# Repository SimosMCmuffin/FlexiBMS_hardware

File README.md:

# Note, this is not the hardware version of the "Lite"-version of the FlexiBMS, but an earlier tested and discontinued/abandoned concept of the BMS design. Lite HW is a new project that was started after this HW project was discontinued and is not currently in open-source circulation HW design wise.

# FlexiBMS_hardware
Open Source BMS developed by Simo Sihvonen (Simos MCmuffin) with the Esk8 community, for the Esk8 community.

This project was inspired by Raphael Chang's Battman project's hardware design (https://github.com/raphaelchang/battman-hardware)

More current news and happening related to this project can be found and followed over at the project thread at the electic-skateboard.builders forum: 
http://www.electric-skateboard.builders/t/flexibms-0-2-hw-under-work-flexible-configuration-and-charging-bms/46117

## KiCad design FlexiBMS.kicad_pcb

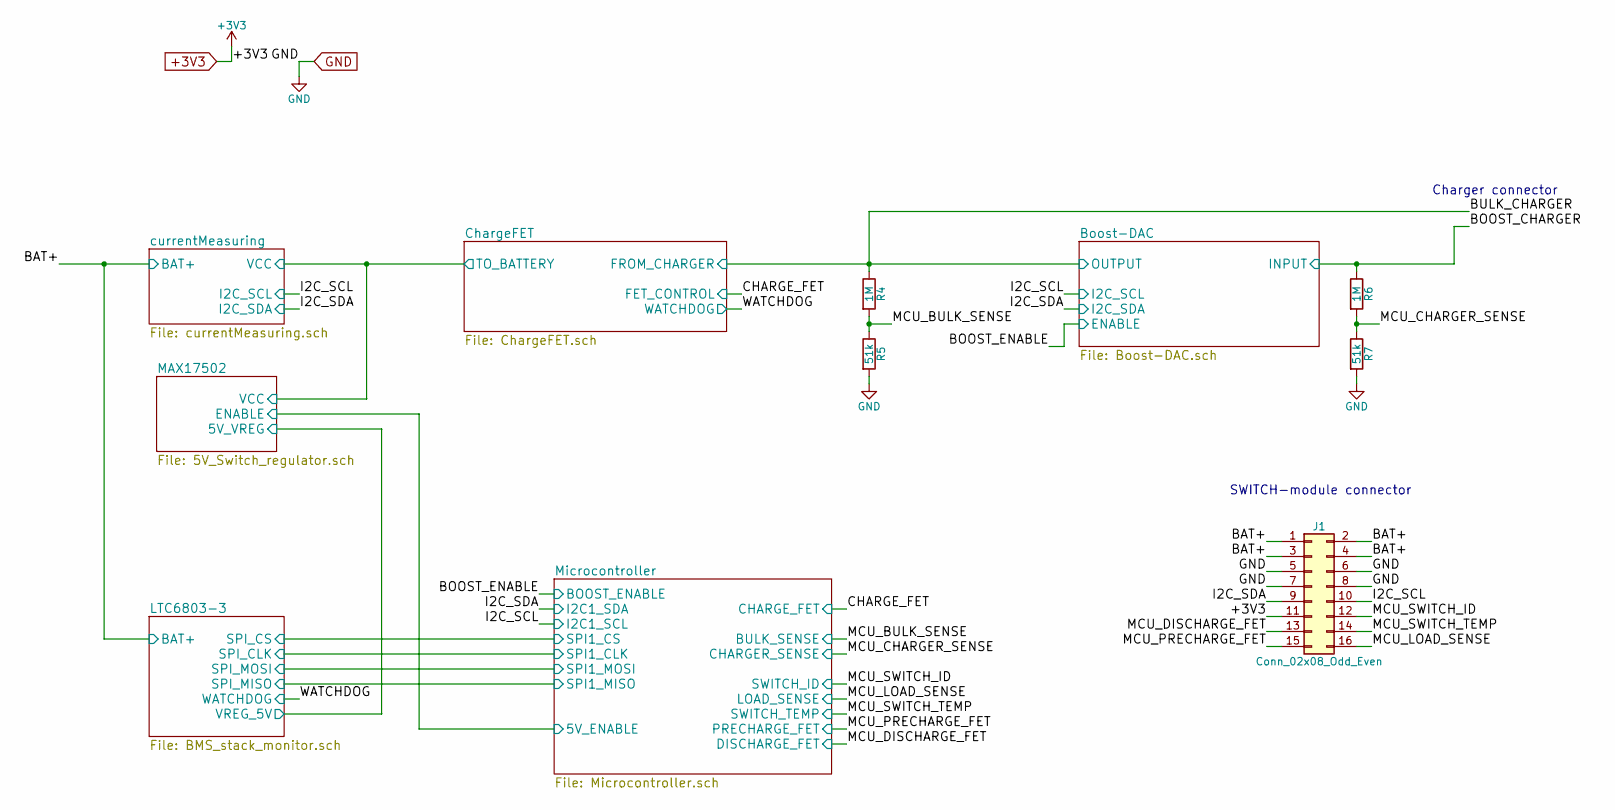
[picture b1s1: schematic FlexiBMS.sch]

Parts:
J1: Conn_02x08_Odd_Even; Pin_Header_Straight_2x08_Pitch2.54mm
R4, R6: 1M; R_0603
R5, R7: 51k; R_0603

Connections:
+3V3: J1.11; also elsewhere on the board
/BAT+: J1.1, J1.2, J1.3, J1.4; also elsewhere on the board
/BOOST_CHARGER: R6.1; also elsewhere on the board
/BULK_CHARGER: R4.1; also elsewhere on the board
/I2C_SCL: J1.10; also elsewhere on the board
/I2C_SDA: J1.9; also elsewhere on the board
/MCU_BULK_SENSE: R4.2, R5.1; also elsewhere on the board
/MCU_CHARGER_SENSE: R6.2, R7.1; also elsewhere on the board
/MCU_DISCHARGE_FET: J1.13; also elsewhere on the board
/MCU_LOAD_SENSE: J1.16; also elsewhere on the board
/MCU_PRECHARGE_FET: J1.15; also elsewhere on the board
/MCU_SWITCH_ID: J1.12; also elsewhere on the board
/MCU_SWITCH_TEMP: J1.14; also elsewhere on the board
GND: J1.5, J1.6, J1.7, J1.8, R5.2, R7.2; also elsewhere on the board

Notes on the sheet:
SWITCH-module connector
Charger connector

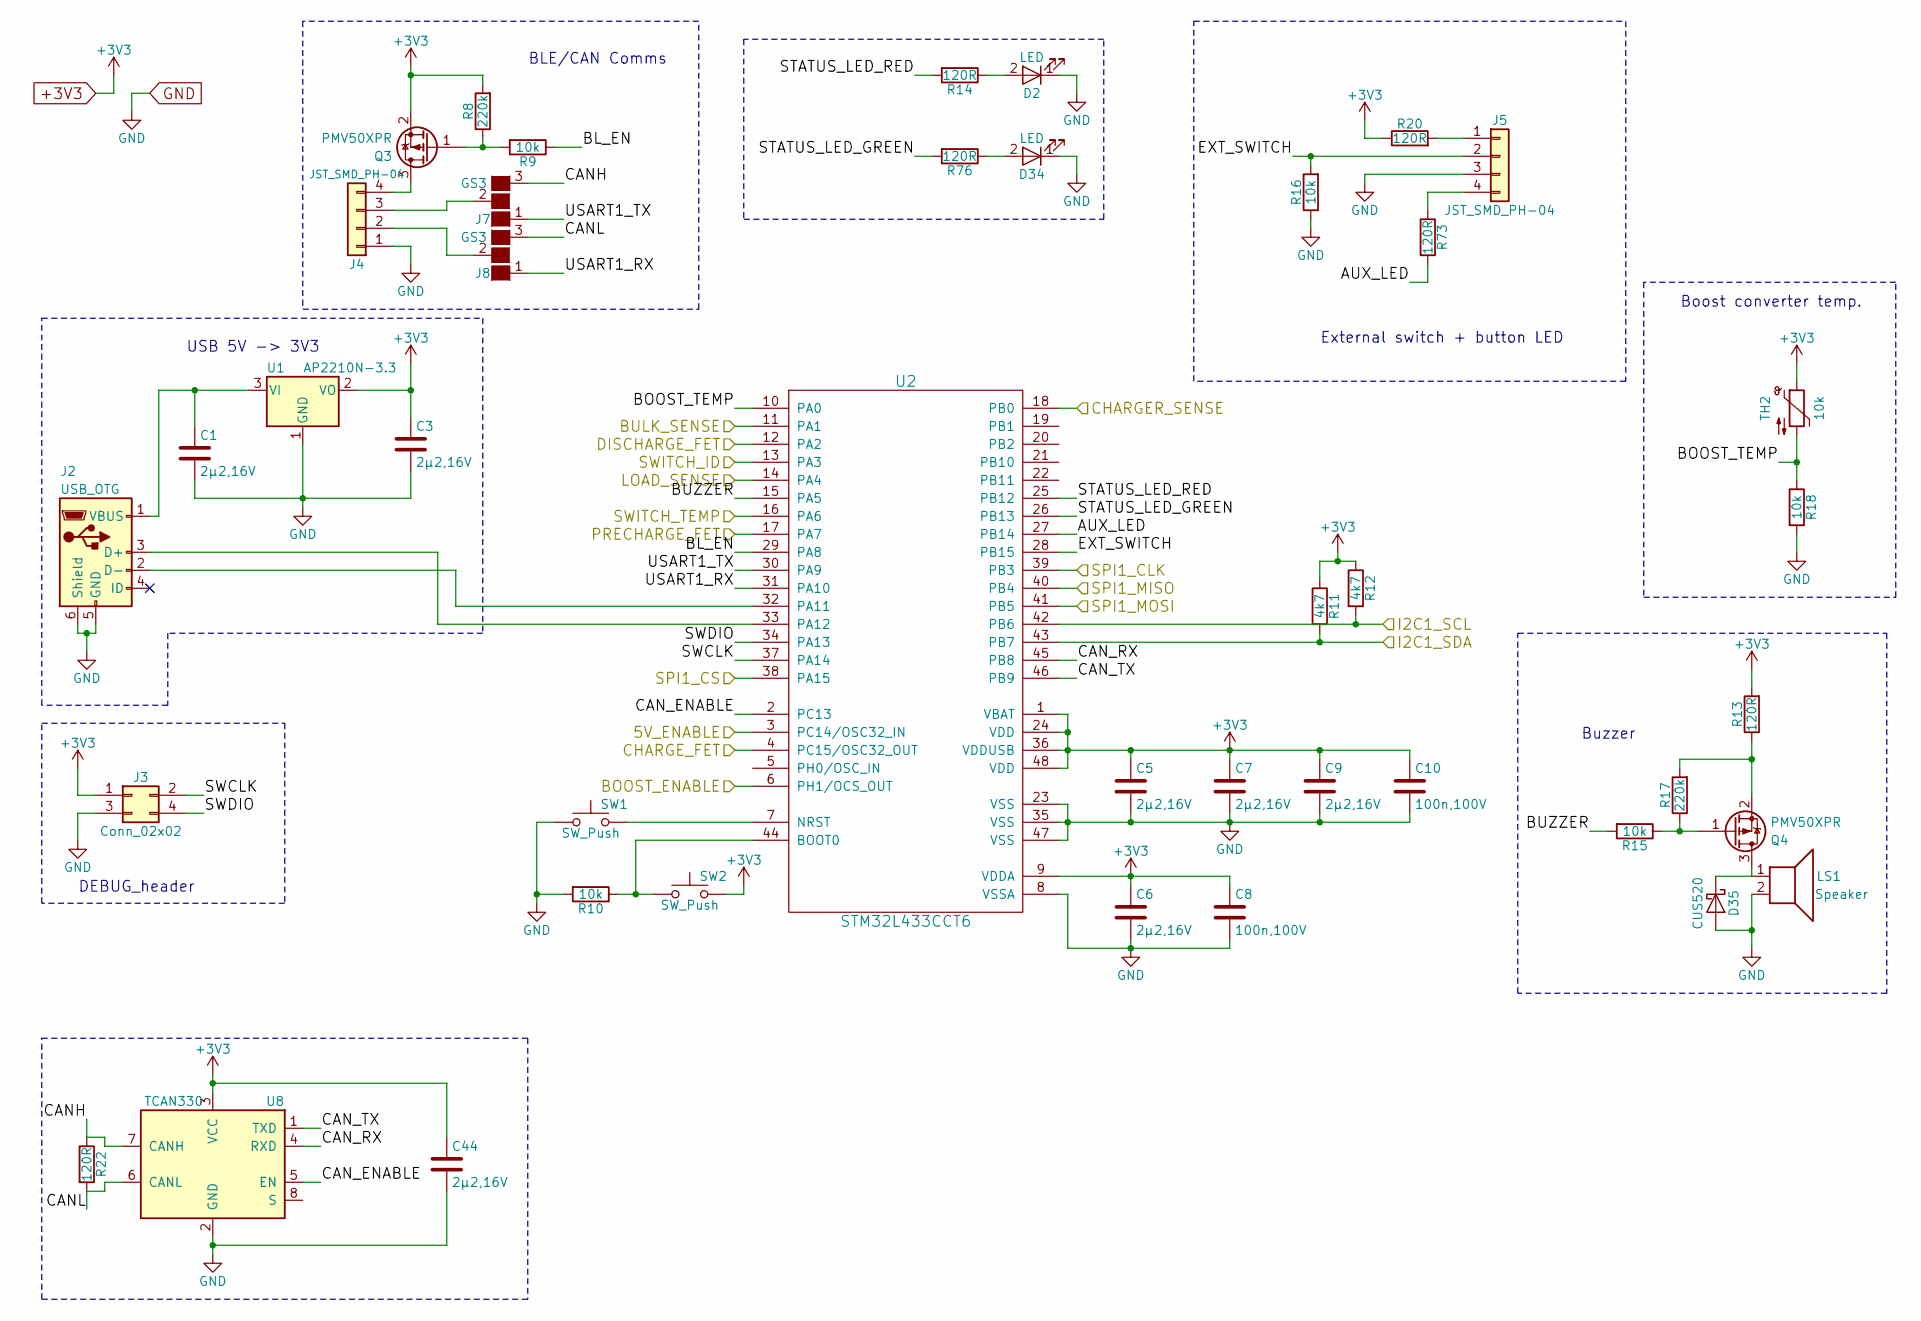
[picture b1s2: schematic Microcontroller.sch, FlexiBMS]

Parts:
C1, C3, C5, C6, C7, C9, C44: 2µ2,16V; C_0603
C8, C10: 100n,100V; C_0603
D2, D34: LED; LED_0603
D35: CUS520; D_SOD-323
J2: USB_OTG; USB_Micro-B_Molex_47346-0001
J3: Conn_02x02; Socket_Strip_Straight_2x02_Pitch2.54mm_SMD
J4, J5: JST_SMD_PH-04; JST_PH_B4B-PH-SM4-TB_04x2.00mm_Straight
J7, J8: GS3
LS1: Speaker; CSS-0575
Q3, Q4: PMV50XPR; SOT-23
R8, R17: 220k; R_0603
R9, R10, R15, R16, R18: 10k; R_0603
R11, R12: 4k7; R_0603
R13, R14, R20, R22, R73, R76: 120R; R_0603
SW1, SW2: SW_Push; SW_SPST_PTS810
TH2: 10k; R_0603
U1: AP2210N-3.3; SOT-23
U2: STM32L433CCT6; LQFP-48_7x7mm_Pitch0.5mm
U8: TCAN330; SOT-23-8

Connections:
+3V3: C3.1, C5.1, C6.1, C7.1, C8.1, C9.1, C10.1, C44.1, J3.1, Q3.2 (S), R8.2, R11.1, R12.1, R13.2, R20.1, SW2.2, TH2.1, U1.2 (VO), U2.1 (VBAT), U2.9 (VDDA), U2.24 (VDD), U2.36 (VDDUSB), U2.48 (VDD), U8.3 (VCC); also elsewhere on the board
/BOOST_ENABLE: U2.6 (PH1/OCS_OUT); also elsewhere on the board
/CHARGE_FET: U2.4 (PC15/OSC32_OUT); also elsewhere on the board
/I2C_SCL: R12.2, U2.42 (PB6); also elsewhere on the board
/I2C_SDA: R11.2, U2.43 (PB7); also elsewhere on the board
/MCU_BULK_SENSE: U2.11 (PA1); also elsewhere on the board
/MCU_CHARGER_SENSE: U2.18 (PB0); also elsewhere on the board
/MCU_DISCHARGE_FET: U2.12 (PA2); also elsewhere on the board
/MCU_LOAD_SENSE: U2.14 (PA4); also elsewhere on the board
/MCU_PRECHARGE_FET: U2.17 (PA7); also elsewhere on the board
/MCU_SWITCH_ID: U2.13 (PA3); also elsewhere on the board
/MCU_SWITCH_TEMP: U2.16 (PA6); also elsewhere on the board
/Microcontroller/5V_ENABLE: U2.3 (PC14/OSC32_IN); also elsewhere on the board
/Microcontroller/AUX_LED: R73.2, U2.27 (PB14)
/Microcontroller/BL_EN: R9.1, U2.29 (PA8)
/Microcontroller/BOOST_TEMP: R18.1, TH2.2, U2.10 (PA0)
/Microcontroller/BUZZER: R15.2, U2.15 (PA5)
/Microcontroller/CANH: J7.3 (G3), R22.1, U8.7 (CANH)
/Microcontroller/CANL: J8.3 (G3), R22.2, U8.6 (CANL)
/Microcontroller/CAN_ENABLE: U2.2 (PC13), U8.5 (EN)
/Microcontroller/CAN_RX: U2.45 (PB8), U8.4 (RXD)
/Microcontroller/CAN_TX: U2.46 (PB9), U8.1 (TXD)
/Microcontroller/EXT_SWITCH: J5.2, R16.2, U2.28 (PB15)
/Microcontroller/SPI1_CLK: U2.39 (PB3); also elsewhere on the board
/Microcontroller/SPI1_CS: U2.38 (PA15); also elsewhere on the board
/Microcontroller/SPI1_MISO: U2.40 (PB4); also elsewhere on the board
/Microcontroller/SPI1_MOSI: U2.41 (PB5); also elsewhere on the board
/Microcontroller/STATUS_LED_GREEN: R76.2, U2.26 (PB13)
/Microcontroller/STATUS_LED_RED: R14.2, U2.25 (PB12)
/Microcontroller/SWCLK: J3.2, U2.37 (PA14)
/Microcontroller/SWDIO: J3.4, U2.34 (PA13)
/Microcontroller/USART1_RX: J8.1 (G1), U2.31 (PA10)
/Microcontroller/USART1_TX: J7.1 (G1), U2.30 (PA9)
GND: C1.2, C3.2, C5.2, C6.2, C7.2, C8.2, C9.2, C10.2, C44.2, D2.1 (K), D34.1 (K), D35.2 (A), J2.5 (GND), J2.6 (Shield), J3.3, J4.1, J5.3, LS1.2, R10.2, R16.1, R18.2, SW1.1, U1.1 (GND), U2.8 (VSSA), U2.23 (VSS), U2.35 (VSS), U2.47 (VSS), U8.2 (GND); also elsewhere on the board
unnamed: C1.1, J2.1 (VBUS), U1.3 (VI)
unnamed: D2.2 (A), R14.1
unnamed: D34.2 (A), R76.1
unnamed: D35.1 (K), LS1.1, Q4.3 (D)
unnamed: J2.2 (D-), U2.32 (PA11)
unnamed: J2.3 (D+), U2.33 (PA12)
unnamed: J4.2, J8.2 (G2)
unnamed: J4.3, J7.2 (G2)
unnamed: J4.4, Q3.3 (D)
unnamed: J5.1, R20.2
unnamed: J5.4, R73.1
unnamed: Q3.1 (G), R8.1, R9.2
unnamed: Q4.1 (G), R15.1, R17.1
unnamed: Q4.2 (S), R13.1, R17.2
unnamed: R10.1, SW2.1, U2.44 (BOOT0)
unnamed: SW1.2, U2.7 (NRST)

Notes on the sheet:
Boost converter temp.
External switch + button LED
BLE/CAN Comms
Buzzer
USB 5V -> 3V3
DEBUG_header

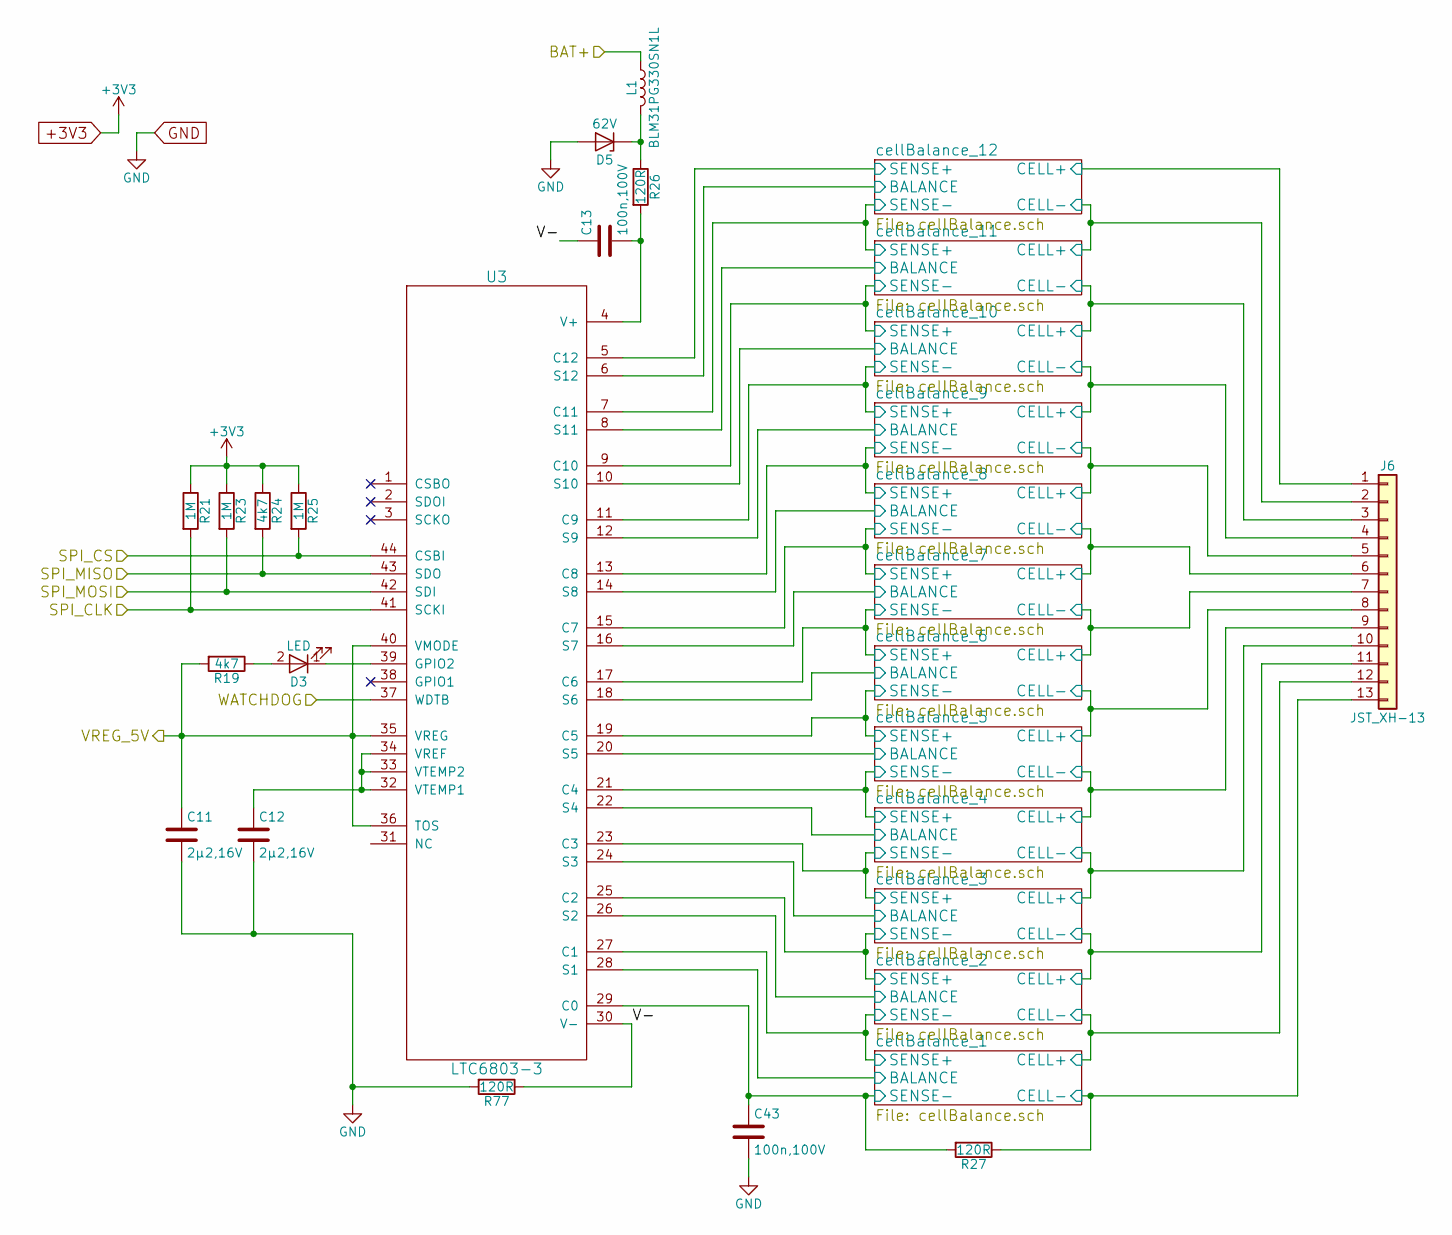
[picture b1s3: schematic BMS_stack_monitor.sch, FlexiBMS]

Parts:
C11, C12: 2µ2,16V; C_0603
C13, C43: 100n,100V; C_0603
D3: LED; LED_0603
D5: 62V; D_SOD-123
J6: JST_XH-13; JST_XH_S13B-XH-A_13x2.50mm_Angled
L1: BLM31PG330SN1L; L_1206
R19, R24: 4k7; R_0603
R21, R23, R25: 1M; R_0603
R26, R77: 120R; R_0603
R27: 120R; R_0402
U3: LTC6803-3; FSOP-44_5.3x13.0mm_Pitch0.5mm

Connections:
+3V3: R21.1, R23.1, R24.1, R25.1; also elsewhere on the board
/BAT+: L1.1; also elsewhere on the board
/LTC6803-3/V-: C13.1, R77.1, U3.30 (V-)
/LTC6803-3/cellBalance_1/BALANCE: U3.28 (S1); also elsewhere on the board
/LTC6803-3/cellBalance_1/CELL+: J6.12; also elsewhere on the board
/LTC6803-3/cellBalance_1/CELL-: J6.13, R27.1; also elsewhere on the board
/LTC6803-3/cellBalance_1/SENSE+: U3.27 (C1); also elsewhere on the board
/LTC6803-3/cellBalance_1/SENSE-: C43.1, R27.2, U3.29 (C0); also elsewhere on the board
/LTC6803-3/cellBalance_2/BALANCE: U3.26 (S2); also elsewhere on the board
/LTC6803-3/cellBalance_2/CELL+: J6.11; also elsewhere on the board
/LTC6803-3/cellBalance_2/SENSE+: U3.25 (C2); also elsewhere on the board
/LTC6803-3/cellBalance_3/BALANCE: U3.24 (S3); also elsewhere on the board
/LTC6803-3/cellBalance_3/CELL+: J6.10; also elsewhere on the board
/LTC6803-3/cellBalance_3/SENSE+: U3.23 (C3); also elsewhere on the board
/LTC6803-3/cellBalance_4/BALANCE: U3.22 (S4); also elsewhere on the board
/LTC6803-3/cellBalance_4/CELL+: J6.9; also elsewhere on the board
/LTC6803-3/cellBalance_4/SENSE+: U3.21 (C4); also elsewhere on the board
/LTC6803-3/cellBalance_5/BALANCE: U3.20 (S5); also elsewhere on the board
/LTC6803-3/cellBalance_5/CELL+: J6.8; also elsewhere on the board
/LTC6803-3/cellBalance_5/SENSE+: U3.19 (C5); also elsewhere on the board
/LTC6803-3/cellBalance_6/BALANCE: U3.18 (S6); also elsewhere on the board
/LTC6803-3/cellBalance_6/CELL+: J6.7; also elsewhere on the board
/LTC6803-3/cellBalance_6/SENSE+: U3.17 (C6); also elsewhere on the board
/LTC6803-3/cellBalance_7/BALANCE: U3.16 (S7); also elsewhere on the board
/LTC6803-3/cellBalance_7/CELL+: J6.6; also elsewhere on the board
/LTC6803-3/cellBalance_7/SENSE+: U3.15 (C7); also elsewhere on the board
/LTC6803-3/cellBalance_8/BALANCE: U3.14 (S8); also elsewhere on the board
/LTC6803-3/cellBalance_8/CELL+: J6.5; also elsewhere on the board
/LTC6803-3/cellBalance_8/SENSE+: U3.13 (C8); also elsewhere on the board
/LTC6803-3/cellBalance_9/BALANCE: U3.12 (S9); also elsewhere on the board
/LTC6803-3/cellBalance_9/CELL+: J6.4; also elsewhere on the board
/LTC6803-3/cellBalance_9/SENSE+: U3.11 (C9); also elsewhere on the board
/LTC6803-3/cellBalance_10/BALANCE: U3.10 (S10); also elsewhere on the board
/LTC6803-3/cellBalance_10/CELL+: J6.3; also elsewhere on the board
/LTC6803-3/cellBalance_10/SENSE+: U3.9 (C10); also elsewhere on the board
/LTC6803-3/cellBalance_11/BALANCE: U3.8 (S11); also elsewhere on the board
/LTC6803-3/cellBalance_11/CELL+: J6.2; also elsewhere on the board
/LTC6803-3/cellBalance_11/SENSE+: U3.7 (C11); also elsewhere on the board
/LTC6803-3/cellBalance_12/BALANCE: U3.6 (S12); also elsewhere on the board
/LTC6803-3/cellBalance_12/CELL+: J6.1; also elsewhere on the board
/LTC6803-3/cellBalance_12/SENSE+: U3.5 (C12); also elsewhere on the board
/MAX17502/5V_VREG: C11.1, R19.2, U3.35 (VREG), U3.36 (TOS), U3.40 (VMODE); also elsewhere on the board
/Microcontroller/SPI1_CLK: R21.2, U3.41 (SCKI); also elsewhere on the board
/Microcontroller/SPI1_CS: R25.2, U3.44 (CSBI); also elsewhere on the board
/Microcontroller/SPI1_MISO: R24.2, U3.43 (SDO); also elsewhere on the board
/Microcontroller/SPI1_MOSI: R23.2, U3.42 (SDI); also elsewhere on the board
/WATCHDOG: U3.37 (WDTB); also elsewhere on the board
GND: C11.2, C12.2, C43.2, D5.2 (A), R77.2; also elsewhere on the board
unnamed: C12.1, U3.32 (VTEMP1), U3.33 (VTEMP2), U3.34 (VREF)
unnamed: C13.2, R26.2, U3.4 (V+)
unnamed: D3.1 (K), U3.39 (GPIO2)
unnamed: D3.2 (A), R19.1
unnamed: D5.1 (K), L1.2, R26.1

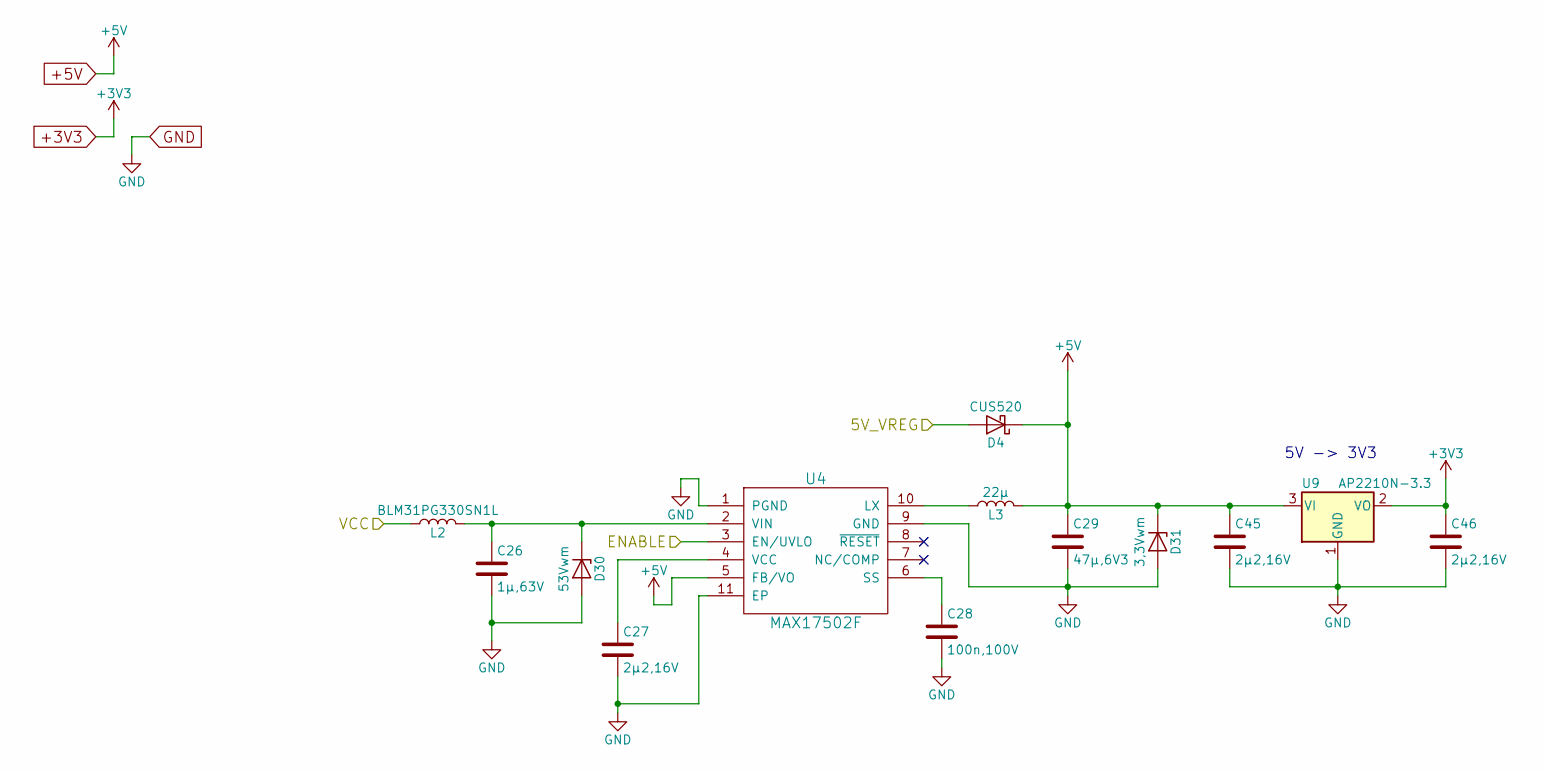
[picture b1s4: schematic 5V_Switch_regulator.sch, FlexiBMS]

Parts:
C26: 1µ,63V; C_1210
C27, C45, C46: 2µ2,16V; C_0603
C28: 100n,100V; C_0603
C29: 47µ,6V3; C_1206
D4: CUS520; D_SOD-323
D30: 53Vwm; D_SMA
D31: 3,3Vwm; D_SOD-123F
L2: BLM31PG330SN1L; L_1206
L3: 22µ; L_1210
U4: MAX17502F; DFN-10-1EP_2x3mm_Pitch0.5mm
U9: AP2210N-3.3; SOT-23

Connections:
+3V3: C46.1, U9.2 (VO); also elsewhere on the board
+5V: C29.1, C45.1, D4.1 (K), D31.1 (K), L3.2, U4.5 (FB/VO), U9.3 (VI)
/ChargeFET/TO_BATTERY: L2.1; also elsewhere on the board
/MAX17502/5V_VREG: D4.2 (A); also elsewhere on the board
/Microcontroller/5V_ENABLE: U4.3 (EN/UVLO); also elsewhere on the board
GND: C26.2, C27.2, C28.2, C29.2, C45.2, C46.2, D30.2 (A), D31.2 (A), U4.1 (PGND), U4.9 (GND), U4.11 (EP), U9.1 (GND); also elsewhere on the board
unnamed: C26.1, D30.1 (K), L2.2, U4.2 (VIN)
unnamed: C27.1, U4.4 (VCC)
unnamed: C28.1, U4.6 (SS)
unnamed: L3.1, U4.10 (LX)

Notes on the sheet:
5V -> 3V3

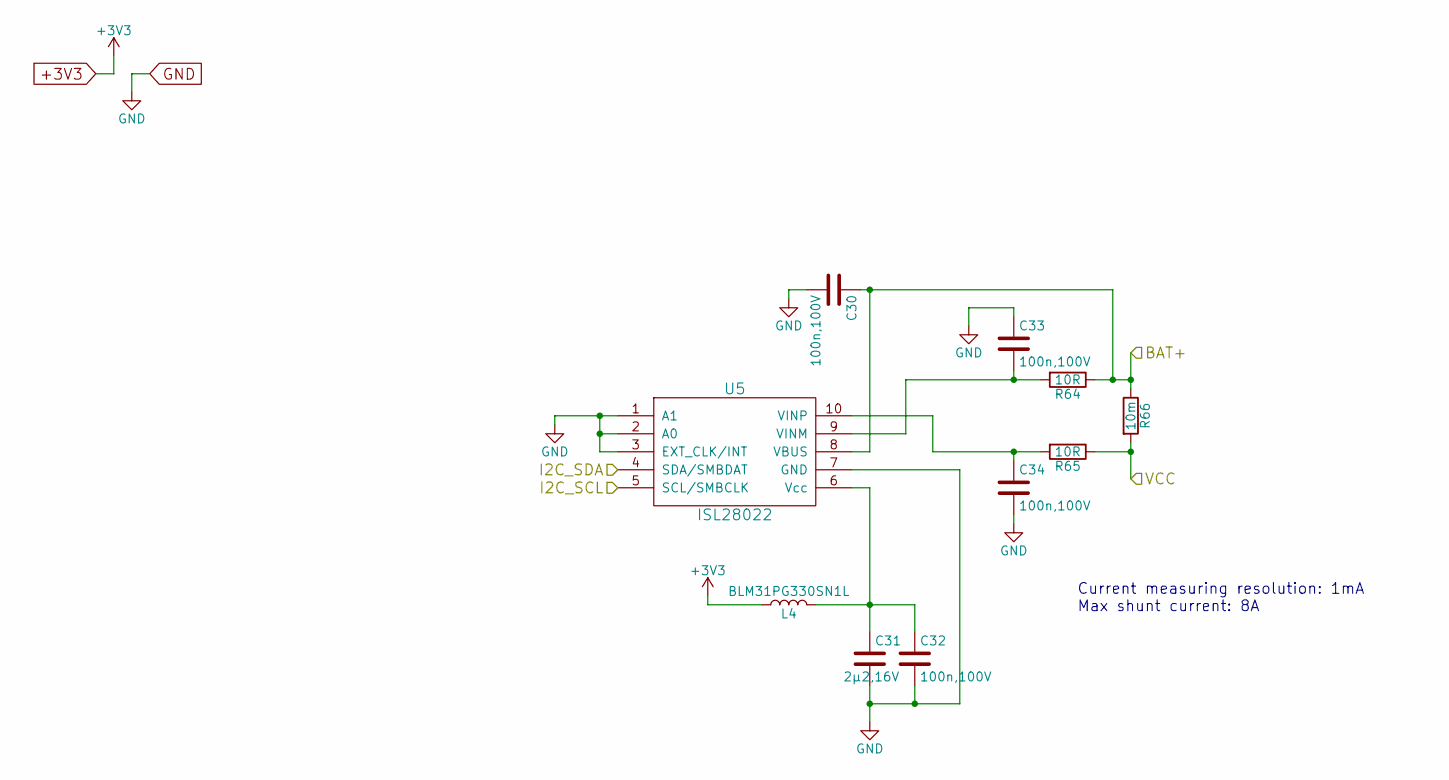
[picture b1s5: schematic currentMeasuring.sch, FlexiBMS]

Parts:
C30, C32, C33, C34: 100n,100V; C_0603
C31: 2µ2,16V; C_0603
L4: BLM31PG330SN1L; L_1206
R64, R65: 10R; R_0603
R66: 10m; R_1206
U5: ISL28022; MSOP-10_3x3mm_Pitch0.5mm

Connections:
+3V3: L4.1; also elsewhere on the board
/BAT+: C30.1, R64.1, R66.1, U5.8 (VBUS); also elsewhere on the board
/ChargeFET/TO_BATTERY: R65.1, R66.2; also elsewhere on the board
/I2C_SCL: U5.5 (SCL/SMBCLK); also elsewhere on the board
/I2C_SDA: U5.4 (SDA/SMBDAT); also elsewhere on the board
GND: C30.2, C31.2, C32.2, C33.1, C34.2, U5.1 (A1), U5.2 (A0), U5.3 (EXT_CLK/INT), U5.7 (GND); also elsewhere on the board
unnamed: C31.1, C32.1, L4.2, U5.6 (Vcc)
unnamed: C33.2, R64.2, U5.9 (VINM)
unnamed: C34.1, R65.2, U5.10 (VINP)

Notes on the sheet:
Current measuring resolution: 1mA Max shunt current: 8A

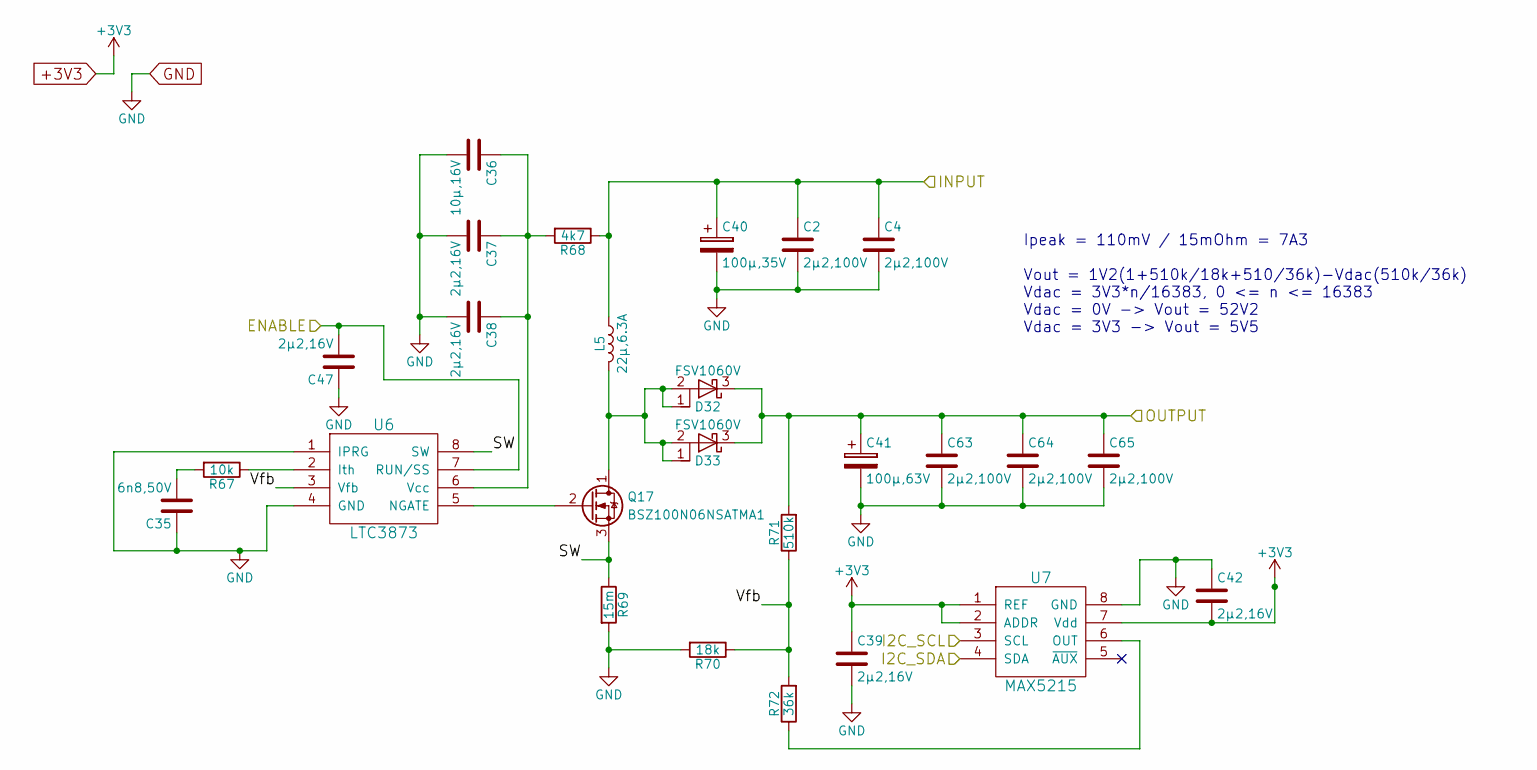
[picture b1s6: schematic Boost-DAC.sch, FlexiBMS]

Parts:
C2, C4, C63, C64, C65: 2µ2,100V; C_1210
C35: 6n8,50V; C_0603
C36: 10µ,16V; C_1206
C37, C38, C39, C42, C47: 2µ2,16V; C_0603
C40: 100µ,35V; CP_Elec_6.3x7.7
C41: 100µ,63V; CP_Elec_10x10
D32, D33: FSV1060V; TO-277A
L5: 22µ,6.3A; HC9
Q17: BSZ100N06NSATMA1; PG-TDSON-8
R67: 10k; R_0603
R68: 4k7; R_0603
R69: 15m; R_1206
R70: 18k; R_0603
R71: 510k; R_0603
R72: 36k; R_0603
U6: LTC3873; TSOT-23-8
U7: MAX5215; MSOP-8_3x3mm_Pitch0.65mm

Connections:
+3V3: C39.1, C42.2, U7.1 (REF), U7.2 (ADDR), U7.7 (Vdd); also elsewhere on the board
/BOOST_CHARGER: C2.1, C4.1, C40.1, L5.1, R68.1; also elsewhere on the board
/BOOST_ENABLE: C47.2, U6.7 (RUN/SS); also elsewhere on the board
/BULK_CHARGER: C41.1, C63.1, C64.1, C65.1, D32.3 (K), D33.3 (K), R71.2; also elsewhere on the board
/Boost-DAC/SW: Q17.3 (S), R69.1, U6.8 (SW)
/Boost-DAC/Vfb: R70.1, R71.1, R72.2, U6.3 (Vfb)
/I2C_SCL: U7.3 (SCL); also elsewhere on the board
/I2C_SDA: U7.4 (SDA); also elsewhere on the board
GND: C2.2, C4.2, C35.1, C36.2, C37.2, C38.2, C39.2, C40.2, C41.2, C42.1, C47.1, C63.2, C64.2, C65.2, R69.2, R70.2, U6.1 (IPRG), U6.4 (GND), U7.8 (GND); also elsewhere on the board
unnamed: C35.2, R67.2
unnamed: C36.1, C37.1, C38.1, R68.2, U6.6 (Vcc)
unnamed: D32.1 (A), D32.2 (A), D33.1 (A), D33.2 (A), L5.2, Q17.1 (D)
unnamed: Q17.2 (G), U6.5 (NGATE)
unnamed: R67.1, U6.2 (Ith)
unnamed: R72.1, U7.6 (OUT)

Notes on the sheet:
Ipeak = 110mV / 15mOhm = 7A3 Vout = 1V2(1+510k/18k+510/36k)-Vdac(510k/36k) Vdac = 3V3*n/16383, 0 <= n <= 16383 Vdac = 0V -> Vout = 52V2 Vdac = 3V3 -> Vout = 5V5

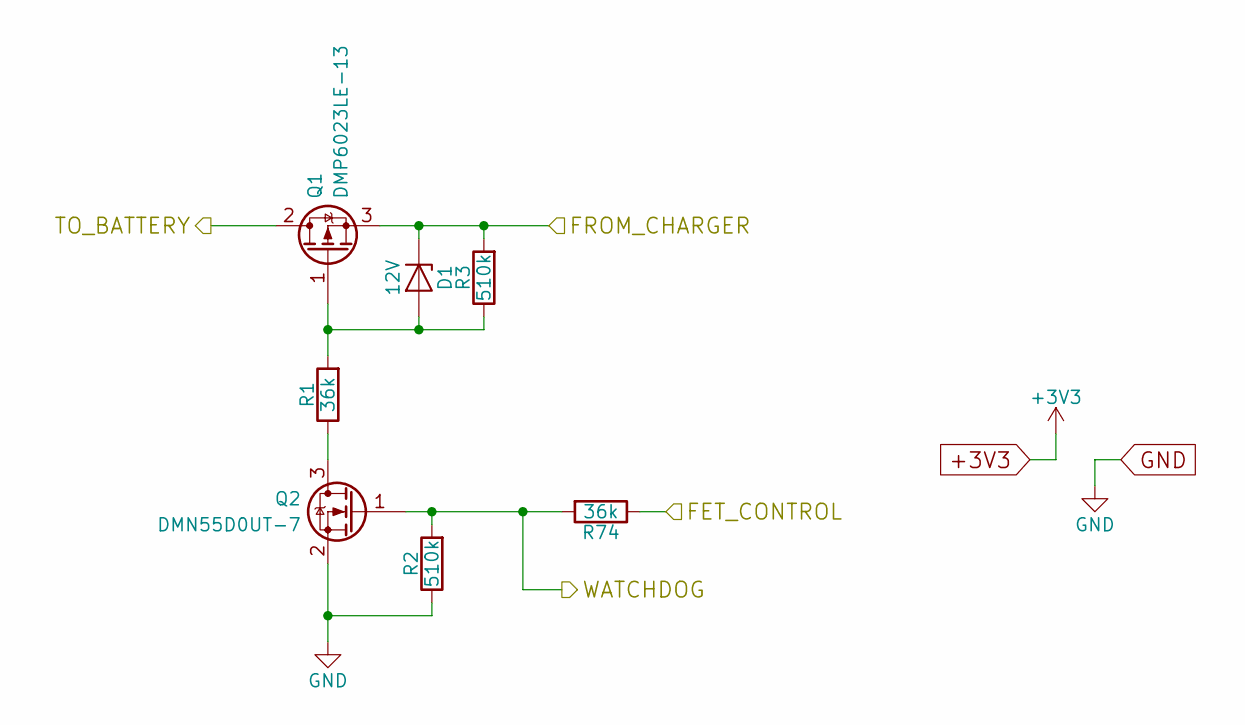
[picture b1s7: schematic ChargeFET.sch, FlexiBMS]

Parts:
D1: 12V; D_SOD-323
Q1: DMP6023LE-13; SOT-223-3_TabPin2
Q2: DMN55D0UT-7; SOT-523
R1, R74: 36k; R_0603
R2, R3: 510k; R_0603

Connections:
/BULK_CHARGER: D1.1 (K), Q1.3 (S), R3.2; also elsewhere on the board
/CHARGE_FET: R74.1; also elsewhere on the board
/ChargeFET/TO_BATTERY: Q1.2 (D); also elsewhere on the board
/WATCHDOG: Q2.1 (G), R2.2, R74.2; also elsewhere on the board
GND: Q2.2 (S), R2.1; also elsewhere on the board
unnamed: D1.2 (A), Q1.1 (G), R1.2, R3.1
unnamed: Q2.3 (D), R1.1

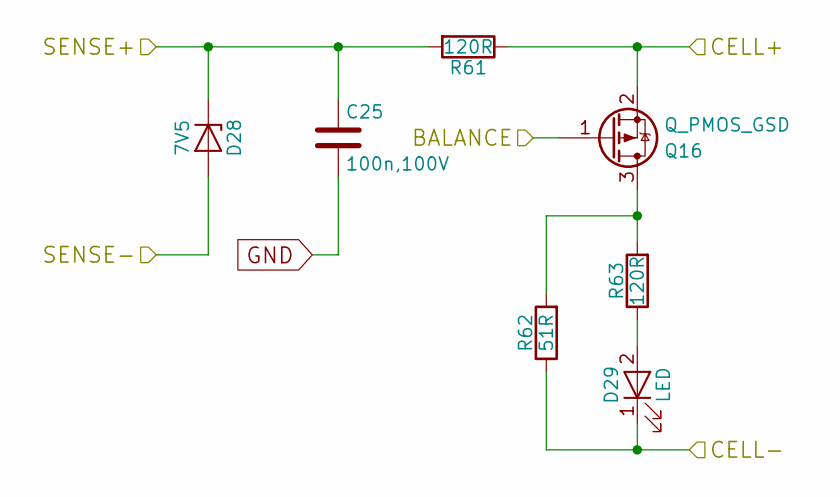
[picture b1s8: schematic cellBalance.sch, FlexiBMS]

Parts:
C14: 100n,100V; C_0603
D6: 7V5; D_SOD-323
D7: LED; LED_0603
Q5: Q_PMOS_GSD; SOT-323_SC-70
R28, R30: 120R; R_0603
R29: 51R; R_0805

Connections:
/LTC6803-3/cellBalance_11/CELL+: D7.1 (K), R29.1; also elsewhere on the board
/LTC6803-3/cellBalance_11/SENSE+: D6.2 (A); also elsewhere on the board
/LTC6803-3/cellBalance_12/BALANCE: Q5.1 (G); also elsewhere on the board
/LTC6803-3/cellBalance_12/CELL+: Q5.2 (S), R28.1; also elsewhere on the board
/LTC6803-3/cellBalance_12/SENSE+: C14.1, D6.1 (K), R28.2; also elsewhere on the board
GND: C14.2; also elsewhere on the board
unnamed: D7.2 (A), R30.1
unnamed: Q5.3 (D), R29.2, R30.2

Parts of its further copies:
C15, C16, C17, C18, C19, C20, C21, C22, C23, C24, C25: 100n,100V; C_0603
D8, D10, D12, D14, D16, D18, D20, D22, D24, D26, D28: 7V5; D_SOD-323
D9, D11, D13, D15, D17, D19, D21, D23, D25, D27, D29: LED; LED_0603
R31, R33, R34, R36, R37, R39, R40, R42, R43, R45, R46, R48, R49, R51, R52, R54, R55, R57, R58, R60, R61, R63: 120R; R_0603
R32, R35, R38, R41, R44, R47, R50, R53, R56, R59, R62: 51R; R_0805

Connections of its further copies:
/LTC6803-3/cellBalance_1/CELL+: D27.1 (K), R59.1, R61.1; also elsewhere on the board
/LTC6803-3/cellBalance_1/CELL-: D29.1 (K), R62.1; also elsewhere on the board
/LTC6803-3/cellBalance_1/SENSE+: C25.1, D26.2 (A), D28.1 (K), R61.2; also elsewhere on the board
/LTC6803-3/cellBalance_1/SENSE-: D28.2 (A); also elsewhere on the board
/LTC6803-3/cellBalance_2/CELL+: D25.1 (K), R56.1, R58.1; also elsewhere on the board
/LTC6803-3/cellBalance_2/SENSE+: C24.1, D24.2 (A), D26.1 (K), R58.2; also elsewhere on the board
/LTC6803-3/cellBalance_3/CELL+: D23.1 (K), R53.1, R55.1; also elsewhere on the board
/LTC6803-3/cellBalance_3/SENSE+: C23.1, D22.2 (A), D24.1 (K), R55.2; also elsewhere on the board
/LTC6803-3/cellBalance_4/CELL+: D21.1 (K), R50.1, R52.1; also elsewhere on the board
/LTC6803-3/cellBalance_4/SENSE+: C22.1, D20.2 (A), D22.1 (K), R52.2; also elsewhere on the board
/LTC6803-3/cellBalance_5/CELL+: D19.1 (K), R47.1, R49.1; also elsewhere on the board
/LTC6803-3/cellBalance_5/SENSE+: C21.1, D18.2 (A), D20.1 (K), R49.2; also elsewhere on the board
/LTC6803-3/cellBalance_6/CELL+: D17.1 (K), R44.1, R46.1; also elsewhere on the board
/LTC6803-3/cellBalance_6/SENSE+: C20.1, D16.2 (A), D18.1 (K), R46.2; also elsewhere on the board
/LTC6803-3/cellBalance_7/CELL+: D15.1 (K), R41.1, R43.1; also elsewhere on the board
/LTC6803-3/cellBalance_7/SENSE+: C19.1, D14.2 (A), D16.1 (K), R43.2; also elsewhere on the board
/LTC6803-3/cellBalance_8/CELL+: D13.1 (K), R38.1, R40.1; also elsewhere on the board
/LTC6803-3/cellBalance_8/SENSE+: C18.1, D12.2 (A), D14.1 (K), R40.2; also elsewhere on the board
/LTC6803-3/cellBalance_9/CELL+: D11.1 (K), R35.1, R37.1; also elsewhere on the board
/LTC6803-3/cellBalance_9/SENSE+: C17.1, D10.2 (A), D12.1 (K), R37.2; also elsewhere on the board
/LTC6803-3/cellBalance_10/CELL+: D9.1 (K), R32.1, R34.1; also elsewhere on the board
/LTC6803-3/cellBalance_10/SENSE+: C16.1, D8.2 (A), D10.1 (K), R34.2; also elsewhere on the board
/LTC6803-3/cellBalance_11/CELL+: R31.1; also elsewhere on the board
/LTC6803-3/cellBalance_11/SENSE+: C15.1, D8.1 (K), R31.2; also elsewhere on the board
GND: C15.2, C16.2, C17.2, C18.2, C19.2, C20.2, C21.2, C22.2, C23.2, C24.2, C25.2; also elsewhere on the board
unnamed: D9.2 (A), R33.1
unnamed: D11.2 (A), R36.1
unnamed: D13.2 (A), R39.1
unnamed: D15.2 (A), R42.1
unnamed: D17.2 (A), R45.1
unnamed: D19.2 (A), R48.1
unnamed: D21.2 (A), R51.1
unnamed: D23.2 (A), R54.1
unnamed: D25.2 (A), R57.1
unnamed: D27.2 (A), R60.1
unnamed: D29.2 (A), R63.1
unnamed 127: R32.2, R33.2; also elsewhere on the board
unnamed 128: R35.2, R36.2; also elsewhere on the board
unnamed 129: R38.2, R39.2; also elsewhere on the board
unnamed 130: R41.2, R42.2; also elsewhere on the board
unnamed 131: R44.2, R45.2; also elsewhere on the board
unnamed 132: R47.2, R48.2; also elsewhere on the board
unnamed 133: R50.2, R51.2; also elsewhere on the board
unnamed 134: R53.2, R54.2; also elsewhere on the board
unnamed 135: R56.2, R57.2; also elsewhere on the board
unnamed 136: R59.2, R60.2; also elsewhere on the board
unnamed 137: R62.2, R63.2; also elsewhere on the board
